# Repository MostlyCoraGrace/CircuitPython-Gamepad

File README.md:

# CircuitPython-Gamepad
a DIY Gamepad made with CircuitPython

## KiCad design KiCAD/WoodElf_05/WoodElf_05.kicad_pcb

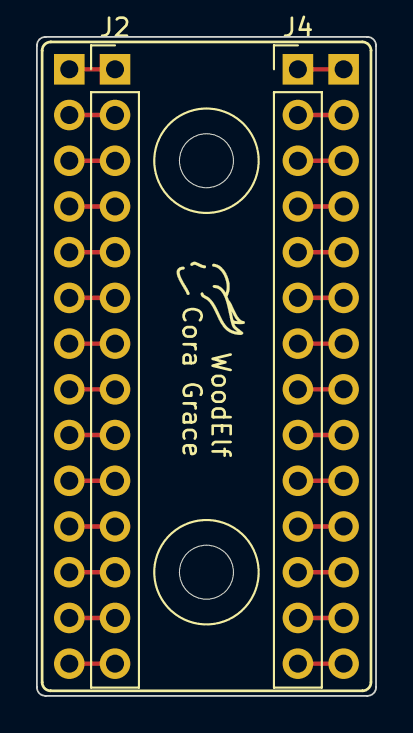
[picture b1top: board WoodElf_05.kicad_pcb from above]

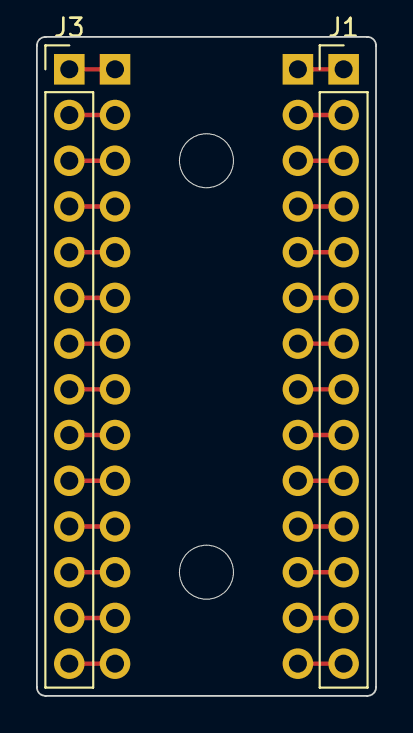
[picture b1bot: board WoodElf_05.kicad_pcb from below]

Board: 2 copper layers, 18.8 x 36.6 mm, 6 parts (2 on the bottom side), 28 nets.

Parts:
J1, J2, J3, J4: Conn_01x14; PinHeader_1x14_P2.54mm_Vertical
SWIN1, SWIN1#2: BTH; BlankThrough-Hole

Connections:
unnamed: J1.1, J2.1
unnamed: J1.2, J2.2
unnamed: J1.3, J2.3
unnamed: J1.4, J2.4
unnamed: J1.5, J2.5
unnamed: J1.6, J2.6
unnamed: J1.7, J2.7
unnamed: J1.8, J2.8
unnamed: J1.9, J2.9
unnamed: J1.10, J2.10
unnamed: J1.11, J2.11
unnamed: J1.12, J2.12
unnamed: J1.13, J2.13
unnamed: J1.14, J2.14
unnamed: J3.1, J4.1
unnamed: J3.2, J4.2
unnamed: J3.3, J4.3
unnamed: J3.4, J4.4
unnamed: J3.5, J4.5
unnamed: J3.6, J4.6
unnamed: J3.7, J4.7
unnamed: J3.8, J4.8
unnamed: J3.9, J4.9
unnamed: J3.10, J4.10
unnamed: J3.11, J4.11
unnamed: J3.12, J4.12
unnamed: J3.13, J4.13
unnamed: J3.14, J4.14

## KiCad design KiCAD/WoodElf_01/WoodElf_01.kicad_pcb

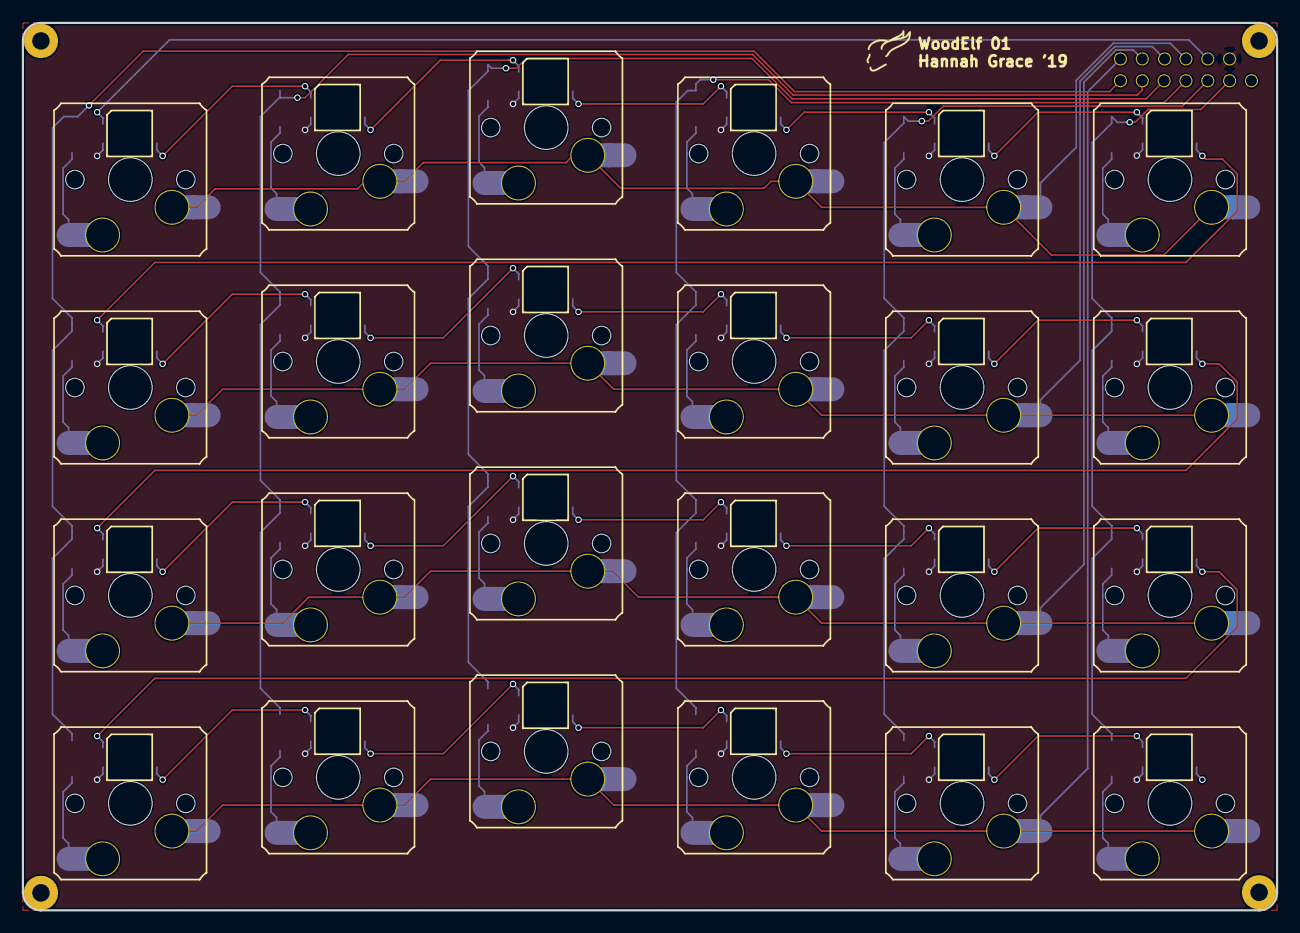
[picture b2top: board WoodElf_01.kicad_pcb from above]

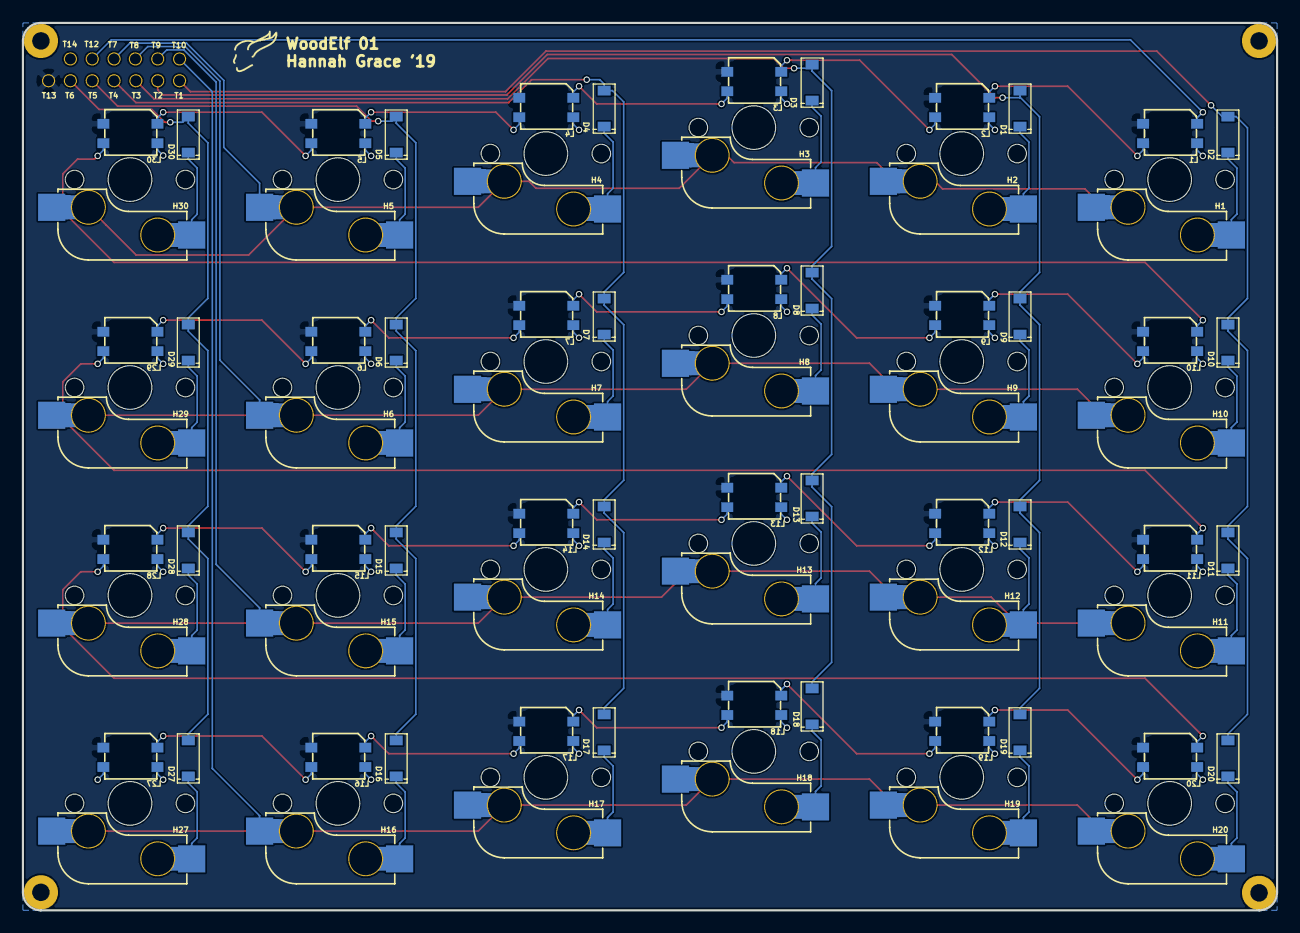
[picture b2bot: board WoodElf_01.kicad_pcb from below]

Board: 2 copper layers, 114.9 x 81.3 mm, 113 parts (24 on the bottom side), 60 nets.

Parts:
D1, D2, D3, D4, D5, D6, D7, D8, D9, D10, D11, D12, D13, D14, D15, D16, D17, D18, D19, D20, D27, D28, D29, D30: DIODE; D_SOD-123
H1, H2, H3, H4, H5, H6, H7, H8, H9, H10, H11, H12, H13, H14, H15, H16, H17, H18, H19, H20, H27, H28, H29, H30: Kailh_HotSwap_SwitchMount; Kailh_HotSwap_Socket
L1, L2, L3, L4, L5, L6, L7, L8, L9, L10, L11, L12, L13, L14, L15, L16, L17, L18, L19, L20, L27, L28, L29, L30: SK6812MINI; LED_SK6812MINI_PLCC4_3.5x3.5mm_P1.75mm
Mount: Mount
Mount#2, Mount#3, Mount#4: Mount
S1, S2, S3, S4, S5, S6, S7, S8, S9, S10, S11, S12, S13, S14, S15, S16, S17, S18, S19, S20, S27, S28, S29, S30: Kailh_RGB_Switch; SW_Cherry_MX1A_1.00u_PCB
T1, T2, T3, T4, T5, T6, T7, T8, T9, T10, T12, T13, T14: BlankThrough-Hole

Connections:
/Col1: D2.2, D10.2, D11.2, D20.2, T1.1
/Col2: D1.2, D9.2, D12.2, D19.2, T2.1
/Col3: D3.2, D8.2, D13.2, D18.2, T3.1
/Col4: D4.2, D7.2, D14.2, D17.2, T4.1
/Col5: D5.2, D6.2, D15.2, D16.2, T5.1
/Col6: D27.2, D28.2, D29.2, D30.2, T6.1
/Din: L1.3, T12.1
/Row1: H1.2, H2.2, H3.2, H4.2, H5.2, H30.2, S1.2, S2.2, S3.2, S4.2, S5.2, S30.2, T7.1
/Row2: H6.2, H7.2, H8.2, H9.2, H10.2, H29.2, S6.2, S7.2, S8.2, S9.2, S10.2, S29.2, T8.1
/Row3: H11.2, H12.2, H13.2, H14.2, H15.2, H28.2, S11.2, S12.2, S13.2, S14.2, S15.2, S28.2, T9.1
/Row4: H16.2, H17.2, H18.2, H19.2, H20.2, H27.2, S16.2, S17.2, S18.2, S19.2, S20.2, S27.2, T10.1
/sheet5D4A5DDF/Din: L3.1, L4.3
/sheet5D4AD70F/Din: L4.1, L5.3
/sheet5D4B503F/Din: L6.3, L7.1
/sheet5D4BCCA4/Din: L7.3, L8.1
/sheet5D4C45D4/Din: L8.3, L9.1
/sheet5D4CBF04/Din: L9.3, L10.1
/sheet5D4D3834/Din: L10.3, L30.1
/sheet5D4DB164/Din: L11.3, L29.1
/sheet5D4E2A94/Din: L11.1, L12.3
/sheet5D4EA3C4/Din: L12.1, L13.3
/sheet5D4F1CF4/Din: L13.1, L14.3
/sheet5D4F9624/Din: L14.1, L15.3
/sheet5D22F5C1/Din: L16.1, L27.3
/sheet5D22F5C7/Din: L15.1, L28.3
/sheet5D22F5CD/Din: L6.1, L29.3
/sheet5D22F5D3/Din: L5.1, L30.3
/sheet5D49E3B8/Din: L2.1, L3.3
/sheet5D51F414/Din: L20.3, L28.1
/sheet5D496A61/Din: L1.1, L2.3
/sheet5D500F54/Din: L16.3, L17.1
/sheet5D517AE4/Din: L19.3, L20.1
/sheet5D5101B4/Din: L18.3, L19.1
/sheet5D508884/Din: L17.3, L18.1
unnamed: D1.1, H2.1, S2.1
unnamed: D2.1, H1.1, S1.1
unnamed: D3.1, H3.1, S3.1
unnamed: D4.1, H4.1, S4.1
unnamed: D5.1, H5.1, S5.1
unnamed: D6.1, H6.1, S6.1
unnamed: D7.1, H7.1, S7.1
unnamed: D8.1, H8.1, S8.1
unnamed: D9.1, H9.1, S9.1
unnamed: D10.1, H10.1, S10.1
unnamed: D11.1, H11.1, S11.1
unnamed: D12.1, H12.1, S12.1
unnamed: D13.1, H13.1, S13.1
unnamed: D14.1, H14.1, S14.1
unnamed: D15.1, H15.1, S15.1
unnamed: D16.1, H16.1, S16.1
unnamed: D17.1, H17.1, S17.1
unnamed: D18.1, H18.1, S18.1
unnamed: D19.1, H19.1, S19.1
unnamed: D20.1, H20.1, S20.1
unnamed: D27.1, H27.1, S27.1
unnamed: D28.1, H28.1, S28.1
unnamed: D29.1, H29.1, S29.1
unnamed: D30.1, H30.1, S30.1
VDD: L1.2, L2.2, L3.2, L4.2, L5.2, L6.2, L7.2, L8.2, L9.2, L10.2, L11.2, L12.2, L13.2, L14.2, L15.2, L16.2, L17.2, L18.2, L19.2, L20.2, L27.2, L28.2, L29.2, L30.2, T13.1
VSS: L1.4, L2.4, L3.4, L4.4, L5.4, L6.4, L7.4, L8.4, L9.4, L10.4, L11.4, L12.4, L13.4, L14.4, L15.4, L16.4, L17.4, L18.4, L19.4, L20.4, L27.4, L28.4, L29.4, L30.4, T14.1

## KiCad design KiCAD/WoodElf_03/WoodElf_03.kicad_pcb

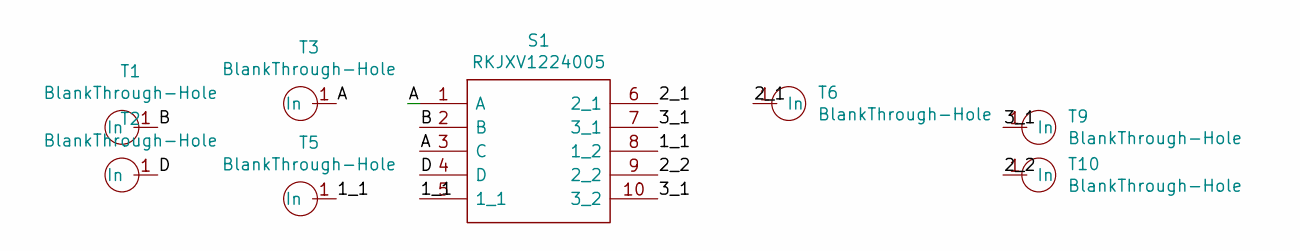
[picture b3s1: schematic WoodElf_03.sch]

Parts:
S1: RKJXV1224005; Mouser Part Number 688-RKJXV1224005
T1, T2, T3, T5, T6, T9, T10: BlankThrough-Hole

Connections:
/1_1: S1.5 (1_1), S1.8 (1_2), T5.1
/2_1: S1.6 (2_1), T6.1
/2_2: S1.9 (2_2), T10.1
/3_1: S1.7 (3_1), S1.10 (3_2), T9.1
/A: S1.1 (A), S1.3 (C), T3.1
/B: S1.2 (B), T1.1
/D: S1.4 (D), T2.1

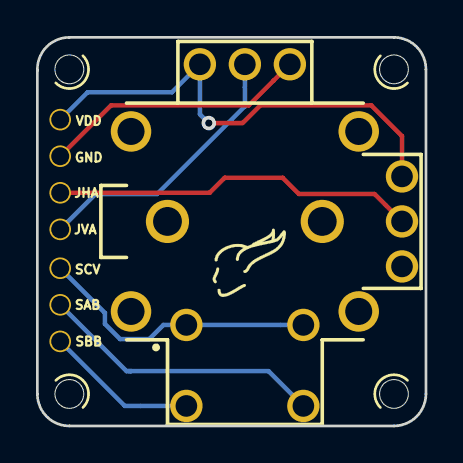
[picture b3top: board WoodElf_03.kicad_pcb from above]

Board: 2 copper layers, 21.6 x 21.6 mm, 12 parts (0 on the bottom side), 7 nets.

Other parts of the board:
Mount: Mount
Mount#2, Mount#3, Mount#4: Mount

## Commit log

2019-01-05 added comments everywhere
    also changed some stuff up; mostly added the macro switching to an actual function instead of using global variables. Oh, and I got rid of some extra code that wasn't needed with the kbd.press events
2019-01-06 changed the connection to the MCP23017 from being per-pin to checking all pins at once
    this messed up a bunch of other things, but its late and i need sleep
2019-01-07 still not sure why its not working, but at least its cleaner now?
2019-01-07 Rename main.py to CircuitPython Code/main.py
2019-01-07 Rename macro2.py to CircuitPython Code/macro2.py
2019-01-07 Rename macro3.py to CircuitPython Code/macro3.py
2019-01-07 Added KiCAD files
2019-01-12 i cant even remember how much i changed here - a lot
2019-01-14 fleshing out some more of the pcb
2019-01-16 more work on the PCB design.
    It's probably done at this point
2019-01-19 made a new single-key pcb
2019-01-20 updated the Tiefling PCB to better match real-world screw options
    Also started mocking up the 3D-printed section
2019-02-11 completely redid the core code
    it now uses a key matrix like any other sane keyboard does. none of this slow-af I2C interface nonsense
2019-02-15 added propper keypress queueing
    and commented a bunch of it
2019-02-15 Toying with the idea to call custom functions
    Toying with the idea to call custom functions within the macro array
2019-02-15 Added button spam macro functionality
2019-02-15 Added button spam function
2019-02-15 got rid of the button spam
    it was poorly put together
2019-02-22 updated PCB to support screws in all corners
    rotated the MS2811 chip to allow for all four corners to be screwed in for support. still need to adjust the holes around the edges though
2019-02-22 switch plate now at first rudimentary pass
    it can support its own weight and hold all the keys. its still hideous, and i dont know if the itsybitsy fits in there, and thers no mount for the analog stick yet.
2019-02-22 updated the PCB to use a 2x2mm SMD RGB LED
    hopefully this works. i want to avoid relying solely on adafruit for their 5x2mm square RGB LED, and i needed more space to allow for the screw mounts.
2019-02-24 re-wrote how the pressed keys are stored to avoid going over the 6-key limit
2019-04-06 fixed up SilkScreens on the PCB
2019-04-07 rotated the ws2811 chip so that everything is at right angles
2019-04-07 fixed up a via that was overlaping a silkscreen
2019-04-07 Cleaned up some more traces
2019-04-07 cleaned up some more traces, updated the silkscreen credit
2019-04-07 cleanup traces
2019-04-16 droped screw sizes for pcb down from M2 to M1.6 to allow for proper sizing of array
2019-04-26 Added a logo
2019-05-04 got rid of the tiny LED and replaced with an SK6812MINI
2019-05-10 Started on the Joystick breakout plate
2019-05-12 reworked the outer edge of the PCB
    turns out i didnt consider how the tiling screw holes would fit with the wire holes - it should all be good now and not interfere with itself
2019-05-12 adjusted the positioning of the screw holes to better allow for a normal keyboard layout
    horizontal offsets of 0.5U or 0.25U should now work without a hitch
2019-06-01 Started on a full-size PCB
2019-06-08 fixed location of joystick pcb in folder
2019-06-16 working out how to mount the joystick to the sandwich
2019-08-17 completely redid everything
    properly this time.
2020-08-10 Old Changes
    This is all the changes i made way back when, at least a year ago. forgot to submit to repo lol
2021-07-17 workin'
